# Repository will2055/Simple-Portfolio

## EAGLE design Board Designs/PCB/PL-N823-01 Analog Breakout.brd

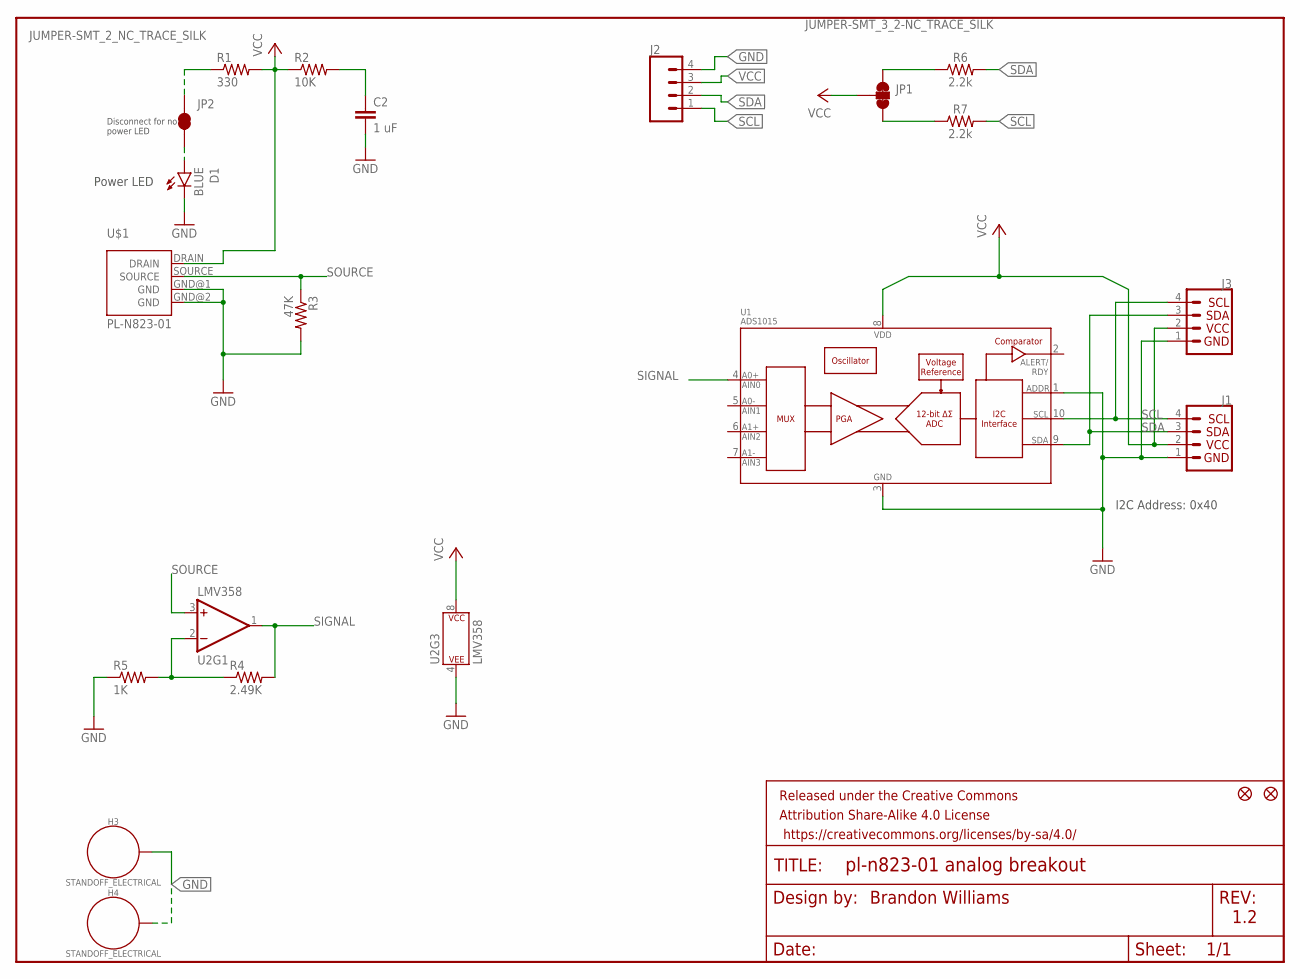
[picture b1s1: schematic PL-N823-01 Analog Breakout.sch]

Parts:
C2: 1 uF; C0603
D1: BLUE; LED-0603
FD1, FD2: FIDUCIALUFIDUCIAL; FIDUCIAL-MICRO
FRAME1: FRAME-LETTERNO_PACKAGE; DUMMY
H3, H4: STANDOFF_ELECTRICAL; STANDOFF-ELECTRICAL
J1, J3: QWIIC_CONNECTORJS-1MM; 1X04_1MM_RA
J2: CONN_041X04_NO_SILK; 1X04_NO_SILK
JP1: JUMPER-SMT_3_2-NC_TRACE_SILK; SMT-JUMPER_3_2-NC_TRACE_SILK
JP2: JUMPER-SMT_2_NC_TRACE_SILK; SMT-JUMPER_2_NC_TRACE_SILK
R1: 330; R0603
R2: 10K; R0603
R3: 47K; R0603
R4: 2.49K; R0603
R5: 1K; R0603
R6, R7: 2.2k; 0603
U1: ADS1015; MSOP10
U2: LMV358; SO08
U$1: PL-N823-01

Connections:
GND: C2.2, D1.C, H3.P1, H4.P1, J1.1 (GND), J2.4, J3.1 (GND), R3.2, R5.1, U1.1 (ADDR), U1.3 (VSS), U2.4 (P$V-), U$1.GND@1 (GND), U$1.GND@2 (GND)
unnamed: R4.1, R5.2, U2.2 (-IN)
unnamed: C2.1, R2.2
unnamed: JP2.1, R1.1
unnamed: JP1.3, R7.1
unnamed: JP1.1, R6.1
unnamed: D1.A, JP2.2
SCL: J1.4 (SCL), J2.1, J3.4 (SCL), R7.2, U1.10 (SCL)
SDA: J1.3 (SDA), J2.2, J3.3 (SDA), R6.2, U1.9 (SDA)
SIGNAL: R4.2, U1.4 (AIN0), U2.1 (OUT)
SOURCE: R3.1, U2.3 (+IN), U$1.SOURCE
VCC: J1.2 (VCC), J2.3, J3.2 (VCC), JP1.2, R1.2, R2.1, U1.8 (VDD), U2.8 (P$V+), U$1.DRAIN

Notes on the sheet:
Brandon Williams
1.2
I2C Address: 0x40
Power LED
Disconnect for no power LED

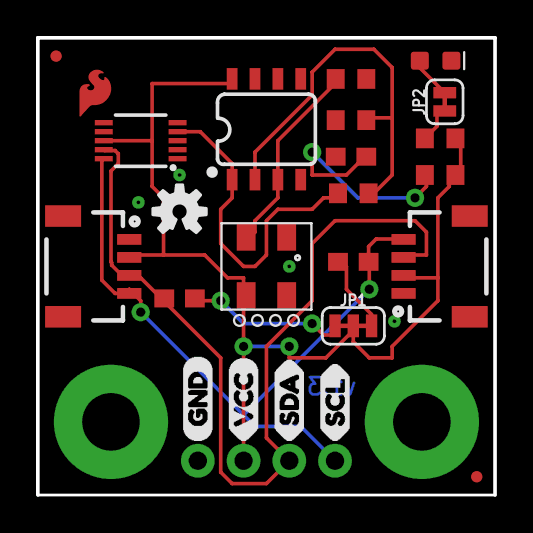
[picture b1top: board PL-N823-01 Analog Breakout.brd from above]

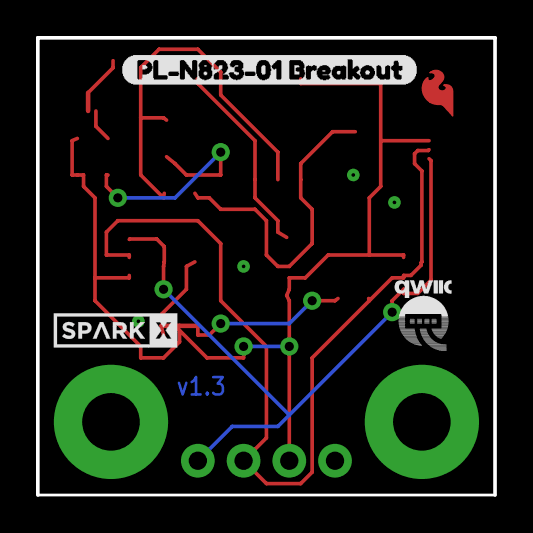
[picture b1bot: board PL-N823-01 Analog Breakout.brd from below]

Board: 2 copper layers, 25.4 x 25.4 mm, 31 parts (3 on the bottom side), 12 nets.

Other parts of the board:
U$2: SFE_LOGO_FLAME_COPPER_EXPOSED_.1
U$3: GND0
U$4: SCL0
U$5: SDA0
U$6: VCC0
U$7: OSHW-LOGO-S
U$8: PL#N823#01_BREAKOUT0
U$9: QWIIC-LOGO-SMALL
U$10: SPARKX-SMALL

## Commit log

2019-04-05 Create home.md
    Landing info page
2019-04-05 Create python_projects.md
    landing page for my python files
2019-04-05 Rename Image Object Recognition.py to python/Image Object Recognition.py
2019-04-05 Added image recognition file
2019-04-05 Rename 89TE_i2c.cpp to C++/89TE_i2c.cpp
2019-04-05 Rename rxm_gps.cpp to C++/rxm_gps.cpp
2019-04-05 Rename Board Designs/PL-N823-01 Analog Breakout.brd to Board Designs/PCB/PL-N823-01 Analog Breakout.brd
2019-04-05 Rename Board Designs/PL-N823-01 Analog Breakout.pro to Board Designs/PCB/PL-N823-01 Analog Breakout.pro
2019-04-05 Rename Board Designs/PL-N823-01 Analog Breakout.sch to Board Designs/PCB/PL-N823-01 Analog Breakout.sch
2019-04-05 Rename Board Designs/PL-N823-01.lbr to Board Designs/PCB/PL-N823-01.lbr

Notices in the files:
parts and their libraries:
SparkFun-Aesthetics: Licensing: Creative Commons ShareAlike 4.0 International - https://creativecommons.org/licenses/by-sa/4.0
SparkFun-Aesthetics: Released under the Creative Commons Attribution Share-Alike 4.0 License
SparkFun-Aesthetics: https://creativecommons.org/licenses/by-sa/4.0
